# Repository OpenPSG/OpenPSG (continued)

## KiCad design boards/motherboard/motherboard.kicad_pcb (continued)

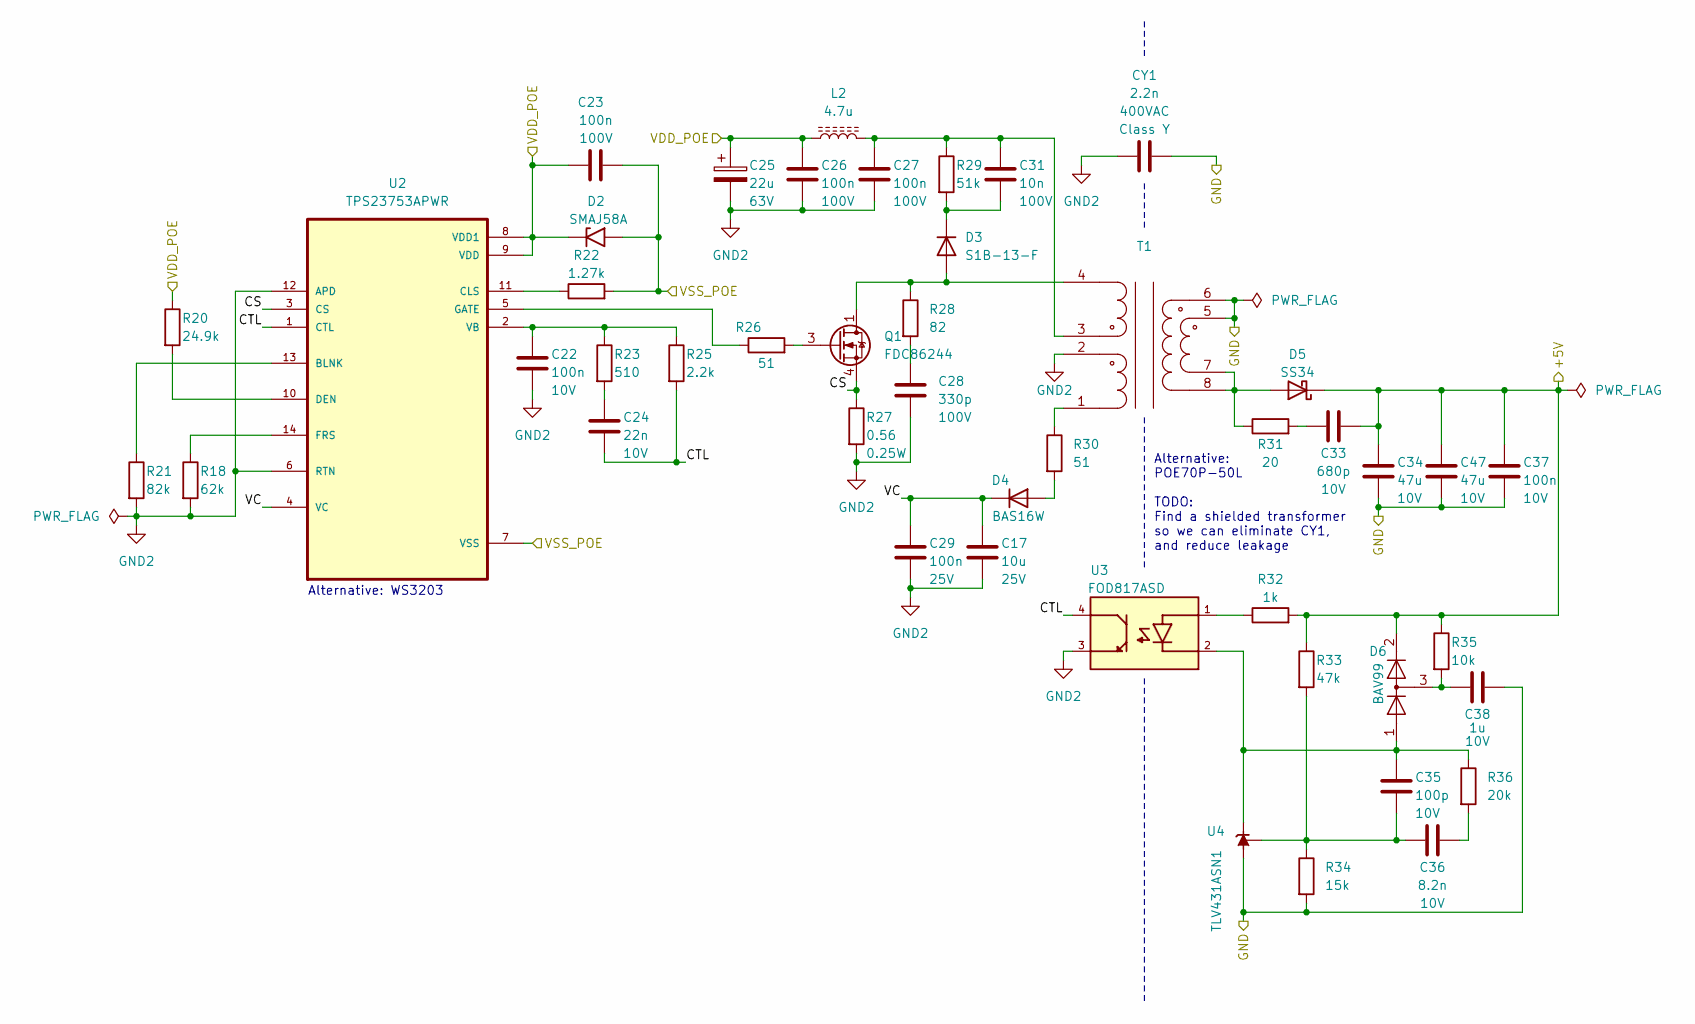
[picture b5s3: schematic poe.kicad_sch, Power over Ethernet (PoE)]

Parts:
C17: 10u; C_0603_1608Metric; Voltage Rating 25V; LCSC PN C96446
C22, C37: 100n; C_0603_1608Metric; Voltage Rating 10V; LCSC PN C14663
C23, C26, C27: 100n; C_0805_2012Metric; Voltage Rating 100V; LCSC PN C28233
C24: 22n; C_0603_1608Metric; Voltage Rating 10V; LCSC PN C21122
C25: 22u; CP_Elec_6.3x7.7; Voltage Rating 63V; LCSC PN C267472
C28: 330p; C_0603_1608Metric; Voltage Rating 100V; LCSC PN C126579
C29: 100n; C_0603_1608Metric; Voltage Rating 25V; LCSC PN C14663
C31: 10n; C_0603_1608Metric; Voltage Rating 100V; LCSC PN C107059
C33: 680p; C_0603_1608Metric; Voltage Rating 10V; LCSC PN C1630
C34, C47: 47u; C_1206_3216Metric; Voltage Rating 10V; LCSC PN C96123
C35: 100p; C_0603_1608Metric; Voltage Rating 10V; LCSC PN C14858
C36: 8.2n; C_0603_1608Metric; Voltage Rating 10V; LCSC PN C1322360
C38: 1u; C_0603_1608Metric; Voltage Rating 10V; LCSC PN C15849
CY1: 2.2n; C_Disc_D10.5mm_W5.0mm_P10.00mm; Voltage Rating 400VAC; LCSC PN C499511
D2: SMAJ58A; D_SMA; LCSC PN C110521
D3: S1B-13-F; D_SMA; LCSC PN C156295
D4: BAS16W; SOT-323_SC-70; LCSC PN C56624
D5: SS34; D_SMA; LCSC PN C8678
D6: BAV99; SOT-23; LCSC PN C2500
L2: 4.7u; L_1008_2520Metric; LCSC PN C82314
Q1: FDC86244; SuperSOT-6; LCSC PN C3290085
R18: 82k; R_0603_1608Metric; LCSC PN C23254
R20: 24.9k; R_0603_1608Metric; LCSC PN C2930080
R21: 62k; R_0603_1608Metric; LCSC PN C23221
R22: 1.27k; R_0603_1608Metric; LCSC PN C2930048
R23: 510; R_0603_1608Metric; LCSC PN C23193
R25: 2.2k; R_0603_1608Metric; LCSC PN C4190
R26, R30: 51; R_0603_1608Metric; LCSC PN C23197
R27: 0.56; R_1206_3216Metric; Power Rating 0.25W; LCSC PN C2907358
R28: 82; R_0603_1608Metric; LCSC PN C23255
R29: 51k; R_0603_1608Metric; LCSC PN C23196
R31: 20; R_0603_1608Metric; LCSC PN C22950
R32: 1k; R_0603_1608Metric; LCSC PN C21190
R33: 47k; R_0603_1608Metric; LCSC PN C25819
R34: 15k; R_0603_1608Metric; LCSC PN C22809
R35: 10k; R_0603_1608Metric; LCSC PN C25804
R36: 20k; R_0603_1608Metric; LCSC PN C4184
T1: HR051067; XFMR-SMD_HR051067; LCSC PN C93830
U2: TPS23753APWR; TSSOP-14_4.4x5mm_P0.65mm; LCSC PN C92115
U3: FOD817ASD; SOIC254P1016X385-4N; LCSC PN C241830
U4: TLV431ASN1; SOT-23-3; LCSC PN C127592

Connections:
+5V: C33.2, C34.1, C37.1, C47.1, D5.1 (K), D6.2 (A), R32.2, R33.1, R35.1; also elsewhere on the board
/Power over Ethernet/CS: Q1.4 (S), R27.1, U2.3 (CS)
/Power over Ethernet/CTL: C24.2, R25.2, U2.1 (CTL), U3.4
/Power over Ethernet/VC: C17.1, C29.1, D4.3 (K), U2.4 (VC)
/VDD_POE: C23.1, C25.1, C26.1, D2.1 (A1), L2.1, R20.1, U2.8 (VDD1), U2.9 (VDD); also elsewhere on the board
/VSS_POE: C23.2, D2.2 (A2), R22.2, U2.7 (VSS); also elsewhere on the board
GND: C34.2, C37.2, C38.2, C47.2, CY1.1, R34.2, T1.5, T1.6, U4.3 (A); also elsewhere on the board
GND2: C17.2, C22.2, C25.2, C26.2, C27.2, C28.2, C29.2, CY1.2, R18.2, R21.2, R27.2, T1.2, U2.6 (RTN), U2.12 (APD), U3.3
unnamed: C24.1, R23.2
unnamed: C27.1, C31.1, L2.2, R29.1, T1.3
unnamed: C28.1, R28.2
unnamed: C33.1, R31.2
unnamed: C36.2, R36.2
unnamed: C38.1, D6.3 (K), R35.2
unnamed: D3.2 (A), Q1.1 (D), Q1.2 (D), Q1.5 (D), Q1.6 (D), R28.1, T1.4
unnamed: C31.2, D3.1 (K), R29.2
unnamed: D4.1 (A), R30.2
unnamed: D5.2 (A), R31.1, T1.7, T1.8
unnamed: Q1.3 (G), R26.2
unnamed: R30.1, T1.1
unnamed: R32.1, U3.1
unnamed: R18.1, U2.13 (BLNK)
unnamed: R22.1, U2.11 (CLS)
unnamed: R20.2, U2.10 (DEN)
unnamed: R21.1, U2.14 (FRS)
unnamed: R26.1, U2.5 (GATE)
unnamed: C22.1, R23.1, R25.1, U2.2 (VB)
unnamed: C35.1, D6.1 (K), R36.1, U3.2, U4.1 (K)
unnamed: C35.2, C36.1, R33.2, R34.1, U4.2 (REF)

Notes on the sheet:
Alternative: POE70P-50L TODO: Find a shielded transformer so we can eliminate CY1, and reduce leakage
Alternative: WS3203

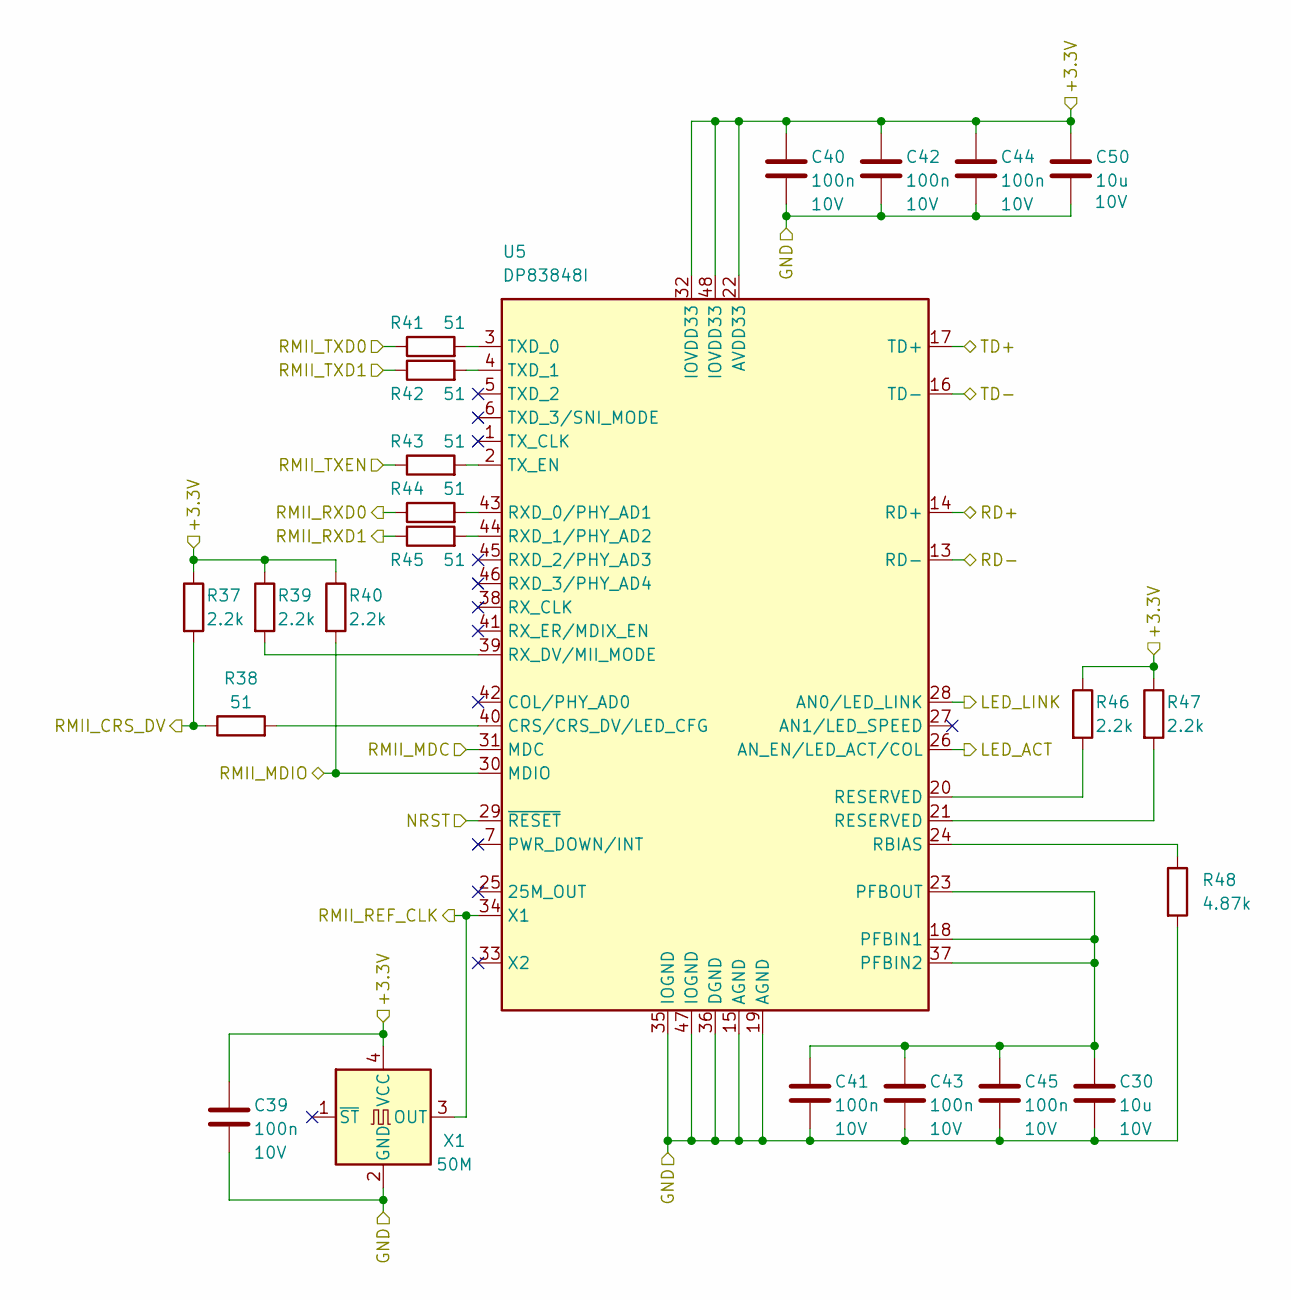
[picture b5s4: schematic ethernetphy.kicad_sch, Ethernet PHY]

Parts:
C30, C50: 10u; C_0603_1608Metric; Voltage Rating 10V; LCSC PN C96446
C39, C40, C41, C42, C43, C44, C45: 100n; C_0603_1608Metric; Voltage Rating 10V; LCSC PN C14663
R37, R39, R40, R46, R47: 2.2k; R_0603_1608Metric; LCSC PN C4190
R38, R41, R42, R43, R44, R45: 51; R_0603_1608Metric; LCSC PN C23197
R48: 4.87k; R_0603_1608Metric; LCSC PN C2998129
U5: DP83848I; LQFP-48_7x7mm_P0.5mm; LCSC PN C12082
X1: 50M; Oscillator_SMD_SeikoEpson_SG8002LB-4Pin_5.0x3.2mm; LCSC PN C7429728

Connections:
+3.3V: C39.1, C40.1, C42.1, C44.1, C50.1, R37.1, R39.1, R40.1, R46.1, R47.1, U5.22 (AVDD33), U5.32 (IOVDD33), U5.48 (IOVDD33), X1.4 (VCC); also elsewhere on the board
/ETH_RX+: U5.14 (RD+); also elsewhere on the board
/ETH_RX-: U5.13 (RD-); also elsewhere on the board
/ETH_TX+: U5.17 (TD+); also elsewhere on the board
/ETH_TX-: U5.16 (TD-); also elsewhere on the board
/Ethernet PHY/LED_ACT: U5.26 (AN_EN/LED_ACT/COL)
/LED_LINK: U5.28 (AN0/LED_LINK); also elsewhere on the board
/NRST: U5.29 (~RESET); also elsewhere on the board
/RMII_CRS_DV: R37.2, R38.1; also elsewhere on the board
/RMII_MDC: U5.31 (MDC); also elsewhere on the board
/RMII_MDIO: R40.2, U5.30 (MDIO); also elsewhere on the board
/RMII_REF_CLK: U5.34 (X1), X1.3 (OUT); also elsewhere on the board
/RMII_RXD0: R44.1; also elsewhere on the board
/RMII_RXD1: R45.1; also elsewhere on the board
/RMII_TXD0: R41.1; also elsewhere on the board
/RMII_TXD1: R42.1; also elsewhere on the board
/RMII_TXEN: R43.1; also elsewhere on the board
GND: C30.2, C39.2, C40.2, C41.2, C42.2, C43.2, C44.2, C45.2, C50.2, R48.2, U5.15 (AGND), U5.19 (AGND), U5.35 (IOGND), U5.36 (DGND), U5.47 (IOGND), X1.2 (GND); also elsewhere on the board
unnamed: R46.2, U5.20 (RESERVED)
unnamed: R47.2, U5.21 (RESERVED)
unnamed: R38.2, U5.40 (CRS/CRS_DV/LED_CFG)
unnamed: C30.1, C41.1, C43.1, C45.1, U5.18 (PFBIN1), U5.23 (PFBOUT), U5.37 (PFBIN2)
unnamed: R48.1, U5.24 (RBIAS)
unnamed: R44.2, U5.43 (RXD_0/PHY_AD1)
unnamed: R45.2, U5.44 (RXD_1/PHY_AD2)
unnamed: R39.2, U5.39 (RX_DV/MII_MODE)
unnamed: R41.2, U5.3 (TXD_0)
unnamed: R42.2, U5.4 (TXD_1)
unnamed: R43.2, U5.2 (TX_EN)

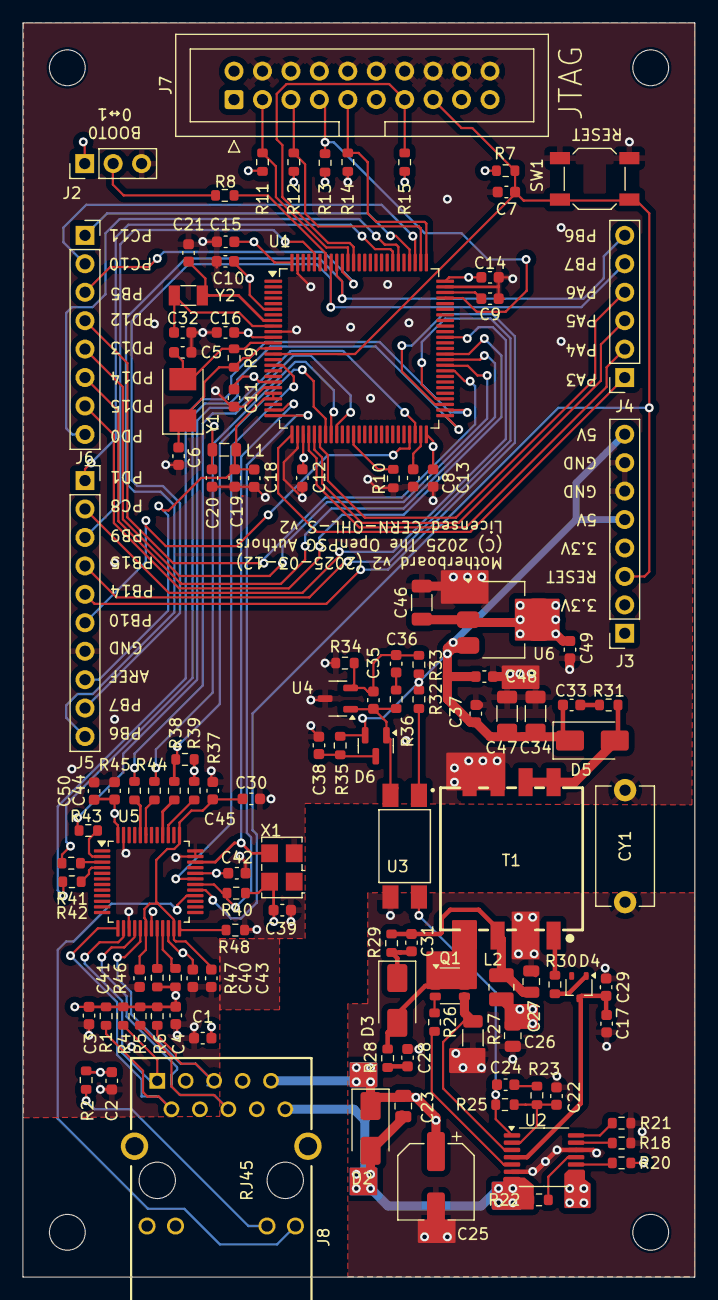
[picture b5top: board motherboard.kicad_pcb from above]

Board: 4 copper layers, 60.0 x 112.0 mm, 124 parts (0 on the bottom side), 92 nets.

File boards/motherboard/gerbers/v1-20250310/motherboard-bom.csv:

"Reference","Value","Footprint","Qty","LCSC PN"
"C1,C2,C3,C4,C7,C10,C11,C12,C13,C14,C15,C16,C18,C20,C22,C29,C37,C39,C40,C41,C42,C43,C44,C45,C48,C49","100n","Capacitor_SMD:C_0603_1608Metric","26","C14663"
"C5,C6","20p","Capacitor_SMD:C_0603_1608Metric","2","C1648"
"C8,C9","2.2u","Capacitor_SMD:C_0603_1608Metric","2","C23630"
"C17,C19,C30","10u","Capacitor_SMD:C_0603_1608Metric","3","C96446"
"C21,C32","12p","Capacitor_SMD:C_0603_1608Metric","2","C38523"
"C23,C26,C27","100n","Capacitor_SMD:C_0603_1608Metric","3","C15725"
"C24","22n","Capacitor_SMD:C_0603_1608Metric","1","C21122"
"C25","22u","Capacitor_SMD:CP_Elec_6.3x7.7","1","C267472"
"C28","330p","Capacitor_SMD:C_0603_1608Metric","1","C126579"
"C31","10n","Capacitor_SMD:C_0603_1608Metric","1","C107059"
"C33","680p","Capacitor_SMD:C_0603_1608Metric","1","C1630"
"C34,C46,C47","47u","Capacitor_SMD:C_0603_1608Metric","3","C96123"
"C35","100p","Capacitor_SMD:C_0603_1608Metric","1","C14858"
"C36","8.2n","Capacitor_SMD:C_0603_1608Metric","1","C1322360"
"C38","1u","Capacitor_SMD:C_0603_1608Metric","1","C15849"
"CY1","2.2n","Capacitor_THT:C_Disc_D10.5mm_W5.0mm_P10.00mm","1","C499511"
"D2","SMAJ58A","Diode_SMD:D_SMA","1","C110521"
"D3","S1B-13-F","Diode_SMD:D_SMA","1","C156295"
"D4","BAS16W","Package_TO_SOT_SMD:SOT-323_SC-70","1","C56624"
"D5","SS34","Diode_SMD:D_SMA","1","C8678"
"D6","BAV99","Package_TO_SOT_SMD:SOT-23","1","C2500"
"J2","Boot Selection","Connector_PinHeader_2.54mm:PinHeader_1x03_P2.54mm_Vertical","1","C2894926"
"J3,J6","Arduino Connector","Connector_PinSocket_2.54mm:PinSocket_1x08_P2.54mm_Vertical","2","C2897371"
"J4","Arduino Connector","Connector_PinSocket_2.54mm:PinSocket_1x06_P2.54mm_Vertical","1","C2897369"
"J5","Arduino Connector","Connector_PinSocket_2.54mm:PinSocket_1x10_P2.54mm_Vertical","1","C2897373"
"J7","JTAG","Connector_IDC:IDC-Header_2x10_P2.54mm_Vertical","1","C5372868"
"J8","HY931147C","footprints:HY931147C","1","C91754"
"L1","4.7u","Inductor_SMD:L_0805_2012Metric","1","C114862"
"L2","4.7u","Inductor_SMD:L_1008_2520Metric","1","C82314"
"Q1","FDC86244","Package_TO_SOT_SMD:SuperSOT-6","1","C3290085"
"R1,R4,R5,R6,R26,R30,R38,R41,R42,R43,R44,R45","51","Resistor_SMD:R_0603_1608Metric","12","C23197"
"R2,R23","510","Resistor_SMD:R_0603_1608Metric","2","C23193"
"R7,R8,R10,R11,R12,R13,R14,R15,R35","10k","Resistor_SMD:R_0603_1608Metric","9","C25804"
"R9","1M","Resistor_SMD:R_0603_1608Metric","1","C22935"
"R18","82k","Resistor_SMD:R_0603_1608Metric","1","C23254"
"R20","24.9k","Resistor_SMD:R_0603_1608Metric","1","C2930080"
"R21","62k","Resistor_SMD:R_0603_1608Metric","1","C23221"
"R22","1.27k","Resistor_SMD:R_0603_1608Metric","1","C2930048"
"R25,R37,R39,R40,R46,R47","2.2k","Resistor_SMD:R_0603_1608Metric","6","C4190"
"R27","0.56","Resistor_SMD:R_1206_3216Metric","1","C2907358"
"R28","82","Resistor_SMD:R_0603_1608Metric","1","C23255"
"R29","51k","Resistor_SMD:R_0603_1608Metric","1","C23196"
"R31","20","Resistor_SMD:R_0603_1608Metric","1","C22950"
"R32","1k","Resistor_SMD:R_0603_1608Metric","1","C21190"
"R33","47k","Resistor_SMD:R_0603_1608Metric","1","C25819"
"R34","15k","Resistor_SMD:R_0603_1608Metric","1","C22809"
"R36","20k","Resistor_SMD:R_0603_1608Metric","1","C4184"
"R48","4.87k","Resistor_SMD:R_0603_1608Metric","1","C2998129"
"SW1","Reset","Button_Switch_SMD:SW_Tactile_SPST_NO_Straight_CK_PTS636Sx25SMTRLFS","1","C318938"
"T1","HR051067","footprints:XFMR-SMD_HR051067","1","C93830"
"U1","STM32F407VETx","Package_QFP:LQFP-100_14x14mm_P0.5mm","1","C28730"
"U2","TPS23753APWR","Package_SO:TSSOP-14_4.4x5mm_P0.65mm","1","C92115"
"U3","FOD817ASD","footprints:SOIC254P1016X385-4N","1","C241830"
"U4","TLV431ASN1","Package_TO_SOT_SMD:SOT-23-3","1","C127592"
"U5","DP83848I","Package_QFP:LQFP-48_7x7mm_P0.5mm","1","C12082"
"U6","AMS1117-3.3","Package_TO_SOT_SMD:SOT-223-3_TabPin2","1","C6186"
"X1","50M","Oscillator:Oscillator_SMD_SeikoEpson_SG8002LB-4Pin_5.0x3.2mm","1","C7429728"
"Y1","8M","Crystal:Crystal_SMD_5032-2Pin_5.0x3.2mm","1","C115962"
"Y2","32.768k","Crystal:Crystal_SMD_3215-2Pin_3.2x1.5mm","1","C32346"

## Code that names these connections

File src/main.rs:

/* SPDX-License-Identifier: AGPL-3.0-or-later
 *
 * Copyright (C) 2025 The OpenPSG Authors.
 *
 * This program is free software: you can redistribute it and/or modify
 * it under the terms of the GNU Affero General Public License as published
 * by the Free Software Foundation, either version 3 of the License, or
 * (at your option) any later version.
 *
 * This program is distributed in the hope that it will be useful,
 * but WITHOUT ANY WARRANTY; without even the implied warranty of
 * MERCHANTABILITY or FITNESS FOR A PARTICULAR PURPOSE.  See the
 * GNU Affero General Public License for more details.
 *
 * You should have received a copy of the GNU Affero General Public License
 * along with this program.  If not, see <https://www.gnu.org/licenses/>.
 */

#![cfg_attr(not(test), no_std)]
#![cfg_attr(not(test), no_main)]

use crate::api::RpcHandler;
//use crate::cs1237::{Channel, Config as Cs1237Config, Cs1237, Gain, SamplesPerSecond};
use crate::net_util::generate_mac_address;
use crate::task::TaskSignal;
use crate::time::{clock_gettime, clock_settime, init_time, Timespec};
use core::net::{IpAddr, SocketAddr};
use core::option::Option::*;
use core::result::Result::*;
use defmt::{debug, error, info, warn};
use embassy_executor::Spawner;
use embassy_net::tcp::{Error as TcpReadError, TcpSocket};
use embassy_net::udp::{PacketMetadata, UdpSocket};
use embassy_net::{Stack, StackResources};
use embassy_stm32::eth::generic_smi::GenericSMI;
use embassy_stm32::eth::{Ethernet, PacketQueue};
use embassy_stm32::peripherals::ETH;
use embassy_stm32::rng::Rng;
use embassy_stm32::time::Hertz;
use embassy_stm32::{bind_interrupts, eth, peripherals, rng, Config};
use embassy_sync::blocking_mutex::raw::ThreadModeRawMutex;
use embassy_sync::signal::Signal as EmbassySignal;
use embassy_time::{Duration, Timer};
use embedded_jsonrpc::RpcServer;
use rand_core::RngCore;
use static_cell::StaticCell;
use {defmt_rtt as _, panic_probe as _};

mod api;
mod biquad_filter;
mod cs1237;
mod ncpt;
mod net_util;
mod task;
mod time;

bind_interrupts!(struct Irqs {
    ETH => eth::InterruptHandler;
    RNG => rng::InterruptHandler<peripherals::RNG>;
});

type Device = Ethernet<'static, ETH, GenericSMI>;

const NTP_PORT: u16 = 123;
const NTP_PACKET_SIZE: usize = 48;

#[embassy_executor::task]
async fn net_task(mut runner: embassy_net::Runner<'static, Device>) -> ! {
    runner.run().await
}

#[embassy_executor::task]
async fn timesync_task(stack: Stack<'static>) -> ! {
    let timestamp_gen = TimestampGen::default();
    let context = sntpc::NtpContext::new(timestamp_gen);

    let mut rx_meta = [PacketMetadata::EMPTY; 1];
    let mut rx_buffer = [0; NTP_PACKET_SIZE];
    let mut tx_meta = [PacketMetadata::EMPTY; 1];
    let mut tx_buffer = [0; NTP_PACKET_SIZE];

    let mut socket = UdpSocket::new(
        stack,
        &mut rx_meta,
        &mut rx_buffer,
        &mut tx_meta,
        &mut tx_buffer,
    );
    socket.bind(NTP_PORT).unwrap();

    // Get the address of the network gateway.
    let gateway = stack.config_v4().unwrap().gateway;
    if gateway.is_none() {
        panic!("Expected a gateway address");
    }

    let ntp_addr = SocketAddr::new(IpAddr::V4(gateway.unwrap()), NTP_PORT);

    loop {
        match sntpc::get_time(ntp_addr, &socket, context).await {
            Ok(time) => {
                clock_settime(&Timespec {
                    seconds: time.sec() as u64,
                    micros: (u64::from(time.sec_fraction()) * 1_000_000 / u64::from(u32::MAX))
                        as u32,
                })
                .unwrap();

                debug!("Time synchronized: {:?}", time);
            }
            Err(err) => {
                error!("Time synchronization error: {:?}", err);
            }
        }

        Timer::after(Duration::from_secs(20)).await;
    }
}

#[embassy_executor::main]
async fn main(spawner: Spawner) -> ! {
    debug!("Starting...");

    let mut config = Config::default();
    {
        use embassy_stm32::rcc::*;
        config.rcc.hse = Some(Hse {
            freq: Hertz(8_000_000),
            mode: HseMode::Oscillator,
        });
        config.rcc.pll_src = PllSource::HSE;
        config.rcc.pll = Some(Pll {
            prediv: PllPreDiv::DIV8,
            mul: PllMul::MUL336,
            divp: Some(PllPDiv::DIV2), // 8mhz / 8 * 336 / 2 = 168Mhz.
            divq: Some(PllQDiv::DIV7), // 8mhz / 8 * 336 / 7 = 48Mhz.
            divr: None,
        });
        config.rcc.ahb_pre = AHBPrescaler::DIV1;
        config.rcc.apb1_pre = APBPrescaler::DIV4;
        config.rcc.apb2_pre = APBPrescaler::DIV2;
        config.rcc.sys = Sysclk::PLL1_P;
        config.rcc.ls = LsConfig::default_lse();
    }

    debug!("Initializing clocks...");

    let p = embassy_stm32::init(config);

    // Initialize peripherals
   /*  let ncpt_adc = Cs1237::try_new(
        p.SPI1,
        p.PA5,
        p.PA6,
        p.DMA2_CH3,
        p.DMA2_CH2,
        p.EXTI6,
        Cs1237Config {
            sample_rate: SamplesPerSecond::SPS40,
            gain: Gain::G128,
            channel: Channel::ChannelA,
        },
    )
    .await
    .unwrap();
*/
    // Initialize the RTC.
    debug!("Initializing RTC...");
    init_time(p.RTC);

    // Generate random seed.
    debug!("Generating random ethernet seed...");
    let mut rng = Rng::new(p.RNG, Irqs);
    let mut seed = [0; 8];
    rng.fill_bytes(&mut seed);
    let seed = u64::from_le_bytes(seed);

    // Initialize Ethernet device.
    debug!("Initializing Ethernet device...");
    let mac_addr = generate_mac_address();

    static PACKETS: StaticCell<PacketQueue<4, 4>> = StaticCell::new();
    let packet_queue = PACKETS.init(PacketQueue::<4, 4>::new());

    debug!("Bringing up Ethernet device...");

    let device = Ethernet::new(
        packet_queue,
        p.ETH,
        Irqs,
        p.PA1,
        p.PA2,
        p.PC1,
        p.PA7,
        p.PC4,
        p.PC5,
        p.PB12,
        p.PB13,
        p.PB11,
        GenericSMI::new(1), // The default dp83848 address is "1" unlike the LAN8742 which is "0".
        mac_addr,
    );

    // Acquire network configuration using DHCP.
    let config = embassy_net::Config::dhcpv4(embassy_net::DhcpConfig::default());

    // Init network stack
    static RESOURCES: StaticCell<StackResources<3>> = StaticCell::new();
    let (stack, runner) =
        embassy_net::new(device, config, RESOURCES.init(StackResources::new()), seed);

    // Launch network task
    spawner.spawn(net_task(runner)).unwrap();

    // Ensure DHCP configuration is up before trying connect
    stack.wait_config_up().await;

    // Begin synchronizing time with NTP server.
    spawner.spawn(timesync_task(stack)).unwrap();

    // Create JSON-RPC server
    static RPC_SERVER: StaticCell<RpcServer<'static, TcpReadError>> = StaticCell::new();
    let rpc_server = RPC_SERVER.init_with(RpcServer::new);

    // Task signals.
    static NCPT_SAMPLING_TASK_SIGNALS: StaticCell<EmbassySignal<ThreadModeRawMutex, TaskSignal>> =
        StaticCell::new();
    let ncpt_sampling_task_signals = NCPT_SAMPLING_TASK_SIGNALS.init_with(EmbassySignal::new);

    // Register handlers.
    static RPC_HANDLER: StaticCell<RpcHandler> = StaticCell::new();
    let rpc_handler = RPC_HANDLER.init_with(|| RpcHandler::new(ncpt_sampling_task_signals));

    rpc_server
        .register_handler("openpsg.*", rpc_handler)
        .unwrap();

    // Launch pressure transducer sampling task.
  /*  spawner
        .spawn(ncpt::sample(
            rpc_server,
            ncpt_sampling_task_signals,
            ncpt_adc,
        ))
        .unwrap();
 */
    let mut rx_buffer = [0; 128]; // Received commands are nice and small.
    let mut tx_buffer = [0; 1460]; // One Ethernet frame worth of data.

    loop {
        let mut socket = TcpSocket::new(stack, &mut rx_buffer, &mut tx_buffer);
        socket.set_timeout(Some(embassy_time::Duration::from_secs(10)));
        socket.set_keep_alive(Some(embassy_time::Duration::from_secs(5)));

        if let Err(e) = socket.accept(80).await {
            warn!("Accept error: {:?}", e);
            continue;
        }

        info!(
            "Received connection from {:?}",
            socket.remote_endpoint().unwrap()
        );

        // Serve the JSON-RPC requests on the socket
        if let Err(e) = rpc_server.serve(&mut socket).await {
            warn!("JSON-RPC error: {:?}", e);
        }

        info!("Connection closed");
    }
}

#[derive(Clone, Copy, Default)]
struct TimestampGen {
    now: u64,
    now_micros: u32,
}

impl sntpc::NtpTimestampGenerator for TimestampGen {
    fn init(&mut self) {
        let tp = clock_gettime().unwrap();
        self.now = tp.seconds;
        self.now_micros = tp.micros;
    }

    fn timestamp_sec(&self) -> u64 {
        self.now
    }

    fn timestamp_subsec_micros(&self) -> u32 {
        self.now_micros
    }
}

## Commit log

2025-02-22 feat: finish motherboard circuit design
2025-02-23 feat: assign footprints
2025-02-26 feat: finalizing up schematic
2025-03-06 feat: first revision of pcb layout
2025-03-11 feat: first release of motherboard
2025-03-11 feat: include placements and bom
2025-04-06 feat: revised motherboard
2025-04-06 feat: add pressure sensor
2025-04-07 feat: add movement sensor
2025-04-08 feat: add eeg breakout
2025-04-08 docs: add some more documentation
2025-04-10 feat: tweak the eeg breakout
2025-04-11 feat: include legendsemi breakout
2025-04-12 refactor: improve ads1292 breakout
2025-04-14 feat: use autodirection transceiver so stm32 bootloader can be used
2025-04-15 feat: add vibration motor biofeedback board
2025-07-23 feat: initial commit
2025-07-23 refactor: improve sensor config dialog
2025-07-24 feat: make edf writer use streams so we don't have to buffer so much in memory
2025-07-24 feat: display edf writer error
2025-07-24 feat: attempt to work around an android issue
2025-07-24 fix: explicitly request read permissions
2025-07-24 fix: file apis are buggy on android
2025-07-25 fix: empty values should not cause record writing to fail
2025-07-25 fix: random bugs in recording
2025-07-25 feat: add a link to the docs
2025-07-30 feat: make tick text more compact and plan for ble scanning of difficult devices
2025-08-04 refactor: rename about to generic help
2025-08-06 fix: ai abort controller slop in channel implementation leading to browser hangs
2025-08-08 refactor: rename to witmotion imu driver
2025-08-08 feat: use LTTB for plot resampling
2025-08-09 fix: issues with follow mode behavior
2025-08-09 feat: use much faster automatic tick generation
2025-08-10 feat: use KLL for calculating signal quantiles for scaling
2025-08-10 feat: use circular recording buffer
2025-08-11 refactor: KLL was not worth it
    the data is too outlier heavy for it to perform well
2025-08-11 feat: add snore signal
2025-08-12 feat: simplify snore processing
2025-08-12 feat: further improve snore processing
2025-08-12 feat: improve help for snore recording options
2025-08-13 refactor: simplify snore mic driver a bit focusing on chrome
2025-08-13 fix: getOutputTimestamp might not be defined
2025-08-14 feat: add generic temperature support and revisit filters
2025-09-21 feat: allow configuring thermometer name
2025-09-22 feat: add reconnect on BLE signal lost functionality
2025-09-22 feat: move sensor type selection into its own dialog instead of multiple buttons
